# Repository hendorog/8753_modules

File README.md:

Modules for HP 8753 VNA.

Initial goal is to make a DIY version of the 85047A test set.

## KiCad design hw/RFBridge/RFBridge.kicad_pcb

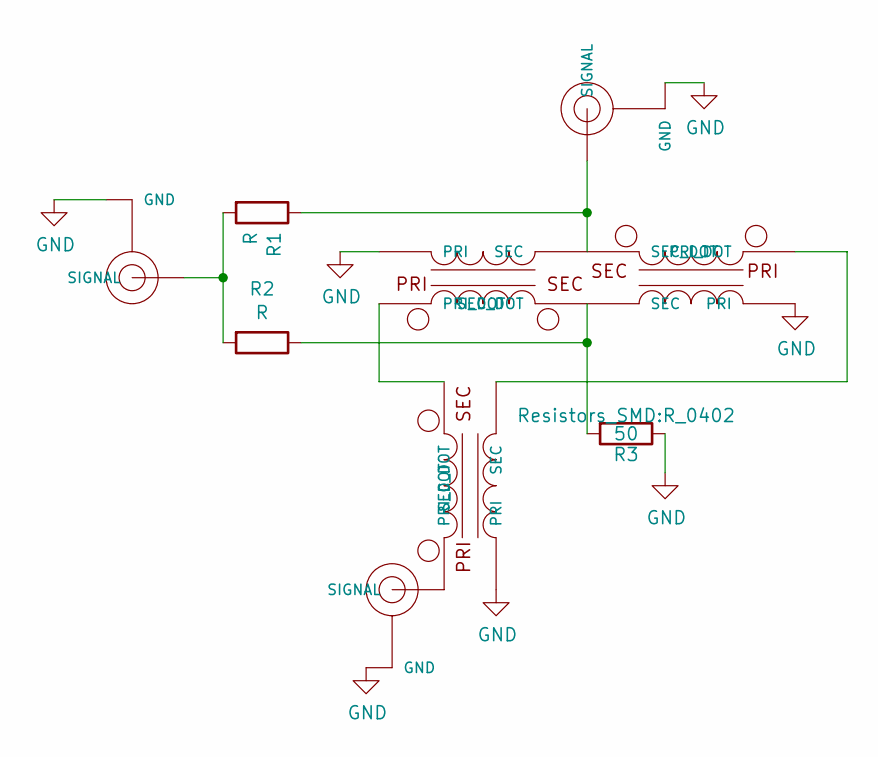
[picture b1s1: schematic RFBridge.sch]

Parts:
R1, R2: R; R_0402
R3: 50; R_0402
SMA1: RF IN; max2870-SMA
SMA2: DUT; max2870-SMA
SMA3: COUP; max2870-SMA
T1, T2, T3: TCM1-63AX+T1; max2870-TCM1-63AX+

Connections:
GND: R3.1, SMA1.GND@ (GND), SMA2.GND@ (GND), SMA3.GND@ (GND), T1.1 (PRI), T1.2 (PRI), T1.5 (PRI), T2.1 (PRI), T2.2 (PRI), T2.5 (PRI), T3.1 (PRI), T3.2 (PRI), T3.5 (PRI)
unnamed: R1.1, SMA2.SIGN (SIGNAL), T1.6 (SEC_DOT), T2.4 (SEC)
unnamed: R1.2, R2.2, SMA1.SIGN (SIGNAL)
unnamed: R2.1, R3.2, T1.4 (SEC), T2.6 (SEC_DOT)
unnamed: SMA3.SIGN (SIGNAL), T3.3 (PRI_DOT)
unnamed: T1.3 (PRI_DOT), T3.4 (SEC)
unnamed: T2.3 (PRI_DOT), T3.6 (SEC_DOT)

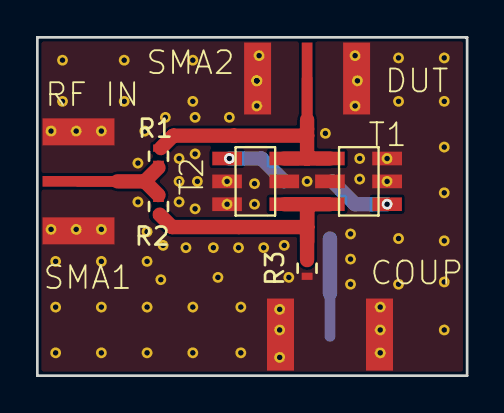
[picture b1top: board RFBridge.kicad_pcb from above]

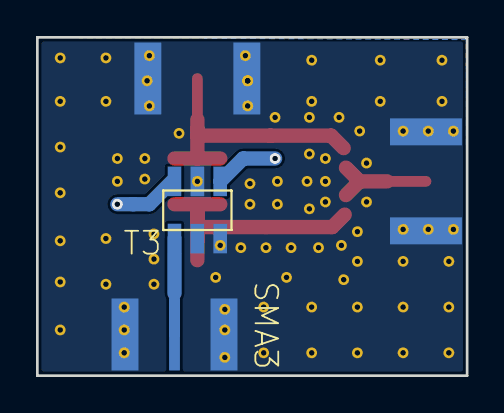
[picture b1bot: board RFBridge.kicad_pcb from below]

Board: 2 copper layers, 23.9 x 18.8 mm, 9 parts (2 on the bottom side), 7 nets.

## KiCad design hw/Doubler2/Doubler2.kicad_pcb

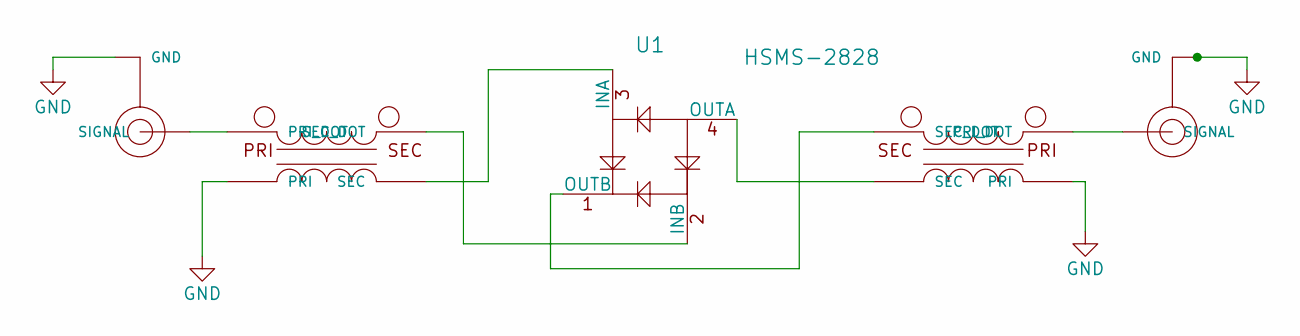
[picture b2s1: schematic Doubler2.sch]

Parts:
SMA1: RF IN; max2870-SMA
SMA2: RF OUT; max2870-SMA
T1, T2: TCM1-63AX+T1; max2870-TCM1-63AX+
U1: HSMS-2828; SOT-143

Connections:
GND: SMA1.GND@ (GND), SMA2.GND@ (GND), T1.1 (PRI), T1.2 (PRI), T1.5 (PRI), T2.1 (PRI), T2.2 (PRI), T2.5 (PRI)
unnamed: SMA1.SIGN (SIGNAL), T1.3 (PRI_DOT)
unnamed: SMA2.SIGN (SIGNAL), T2.3 (PRI_DOT)
unnamed: T1.4 (SEC), U1.3 (INA~)
unnamed: T1.6 (SEC_DOT), U1.2 (INB~)
unnamed: T2.4 (SEC), U1.4 (OUTA~)
unnamed: T2.6 (SEC_DOT), U1.1 (OUTB~)

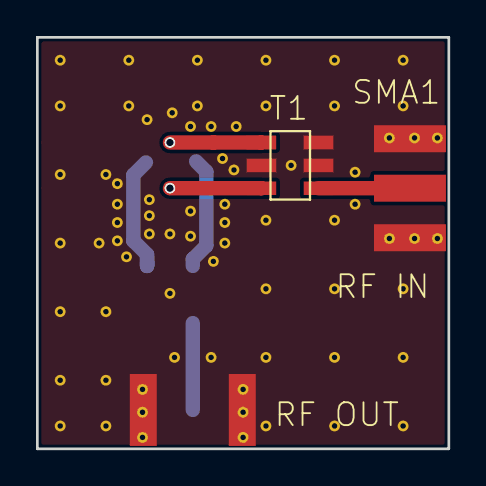
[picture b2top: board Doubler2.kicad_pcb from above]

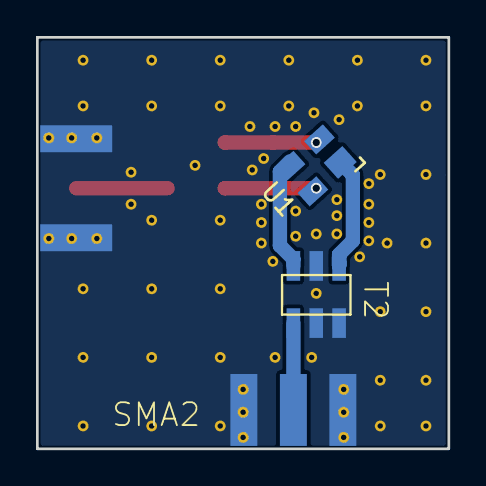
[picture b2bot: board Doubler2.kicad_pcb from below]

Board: 2 copper layers, 22.9 x 22.9 mm, 5 parts (3 on the bottom side), 7 nets.

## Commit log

2017-03-19 Initial import of doubler for 8753
2017-03-23 Add RF Bridge design with double balun to cancel out phase and amp errors in a single balun
